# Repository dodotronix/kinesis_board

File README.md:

# KINESIS BOARD SUPPORTING QMK DRIVER
This project is just small redesign of the Tkint board (https://github.com/kinx-project/kint)

# REQUIREMENTS 
- to be able to properly open the schematics, download following libraries
    - https://github.com/dodotronix/dodo_klibs

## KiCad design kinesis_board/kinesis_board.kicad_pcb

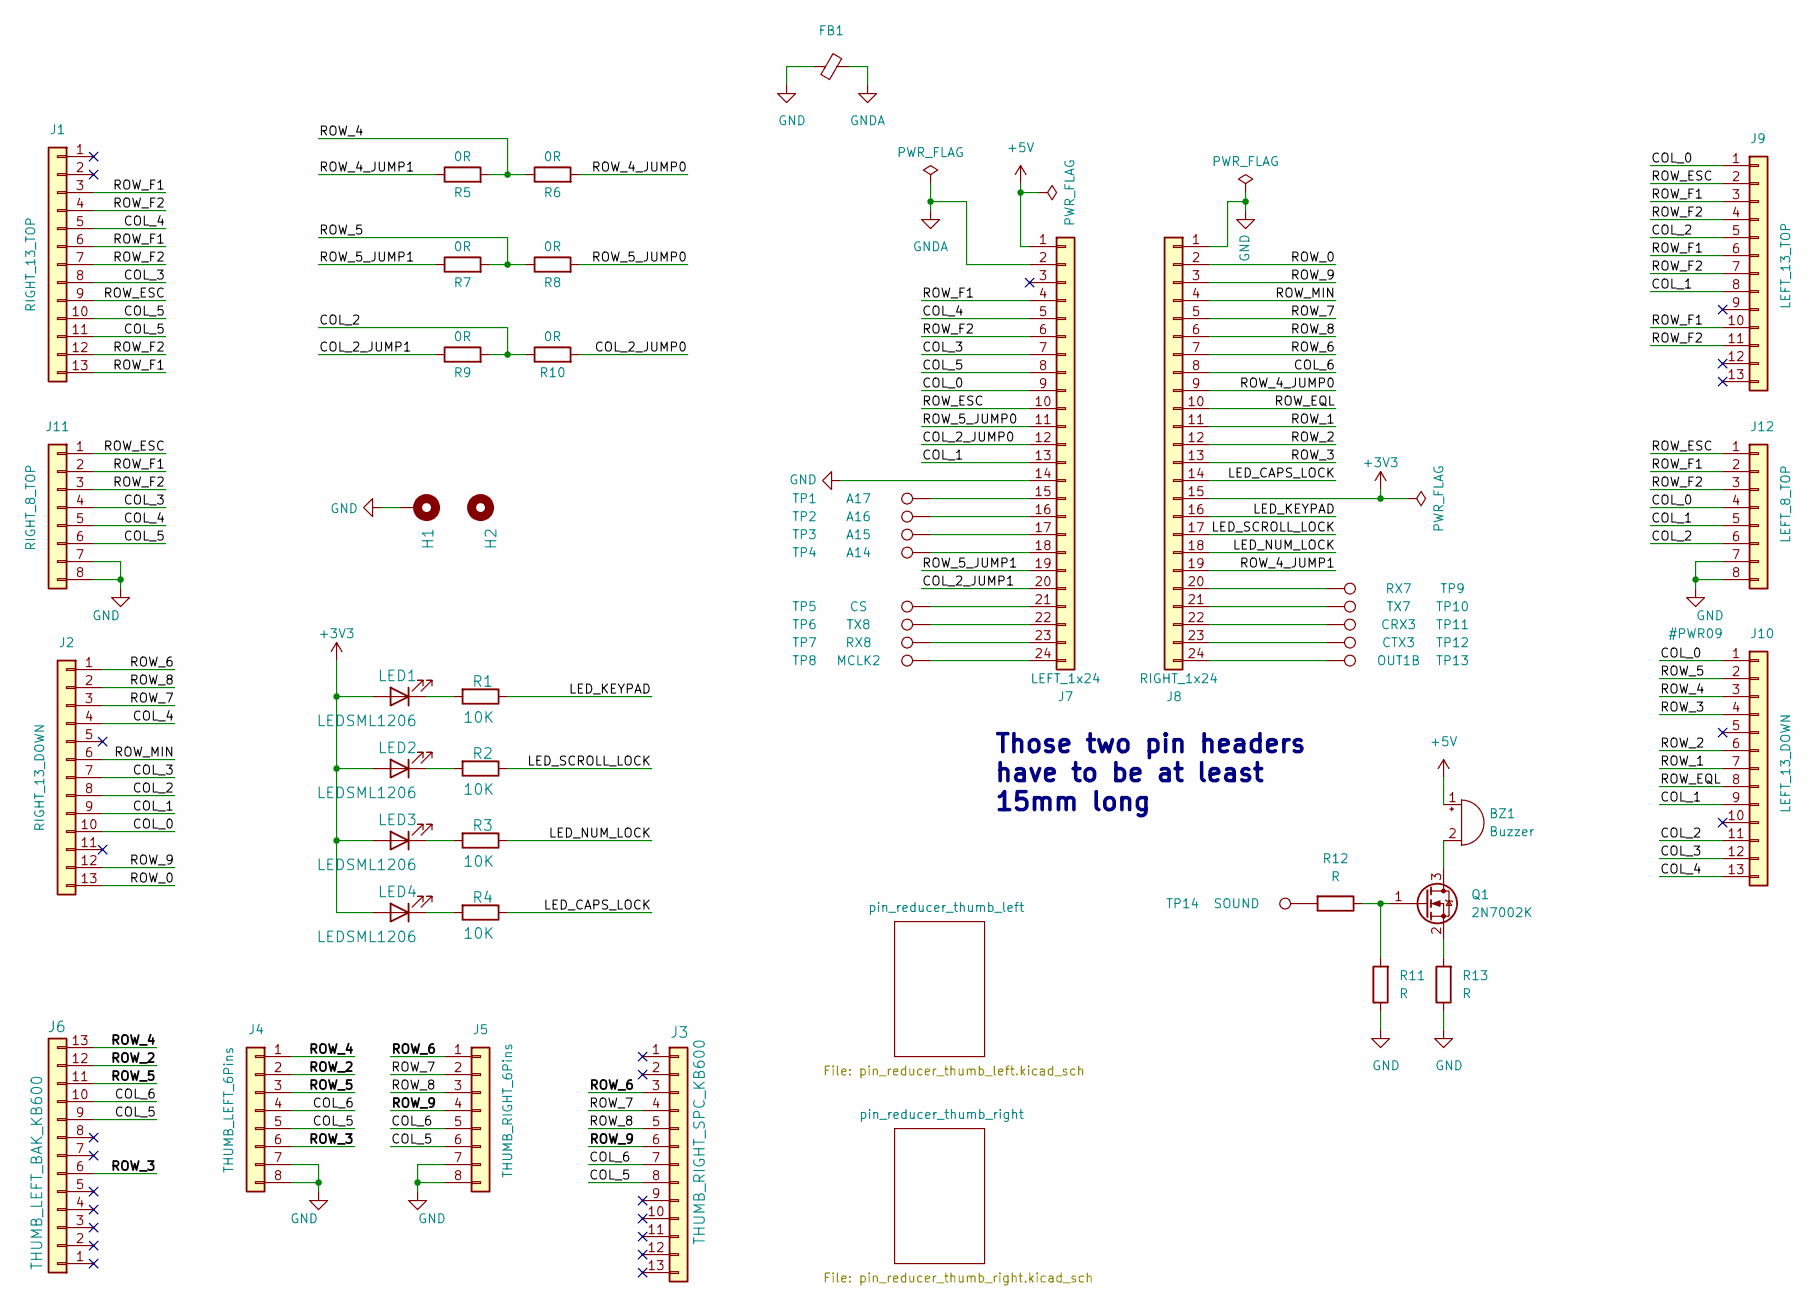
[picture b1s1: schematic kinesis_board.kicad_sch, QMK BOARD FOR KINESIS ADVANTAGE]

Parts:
BZ1: Buzzer; Buzzer_12x9.5RM7.6
FB1: FerriteBead; L_0805_2012Metric_Pad1.05x1.20mm_HandSolder
H1: mounting pad; MountingHole_4.3mm_M4_Pad
H2: mounting pad; MountingHole_6mm
J1: RIGHT_13_TOP; Molex-39-53-2135; MPN 39-53-2135; digikeypn WM14526-ND
J2: RIGHT_13_DOWN; Molex-39-53-2135; MPN 39-53-2135; digikeypn WM14526-ND
J3: THUMB_RIGHT_SPC_KB600; Molex-39-53-2135; MPN 39-53-2135; digikeypn WM14526-ND
J4: THUMB_LEFT_6Pins; 84953-6
J5: THUMB_RIGHT_6Pins; 84953-6
J6: THUMB_LEFT_BAK_KB600; Molex-39-53-2135; MPN 39-53-2135; digikeypn WM14526-ND
J7: LEFT_1x24; PinHeader_1x24_P2.54mm_Vertical
J8: RIGHT_1x24; PinHeader_1x24_P2.54mm_Vertical
J9: LEFT_13_TOP; Molex-39-53-2135; MPN 39-53-2135; digikeypn WM14526-ND
J10: LEFT_13_DOWN; Molex-39-53-2135; MPN 39-53-2135; digikeypn WM14526-ND
J11: RIGHT_8_TOP; 84953-6
J12: LEFT_8_TOP; 84953-6
LED1, LED2, LED3, LED4: LEDSML1206; LED_1206_3216Metric_Pad1.42x1.75mm_HandSolder; MPN APT3216QBC/D; digikeypn 754-1439-1-ND
Q1: 2N7002K; SOT-23
R1, R2, R3, R4: 10K; R_1206_3216Metric_Pad1.30x1.75mm_HandSolder; MPN CRCW120610K0FKEAC; digikeypn 541-3983-1-ND
R5, R6, R7, R8, R9, R10: 0R; R_1206_3216Metric_Pad1.30x1.75mm_HandSolder
R11, R12, R13: R; R_0805_2012Metric_Pad1.20x1.40mm_HandSolder
TP1: A17; TestPoint_Pad_D2.0mm
TP2: A16; TestPoint_Pad_D2.0mm
TP3: A15; TestPoint_Pad_D2.0mm
TP4: A14; TestPoint_Pad_D2.0mm
TP5: CS; TestPoint_Pad_D2.0mm
TP6: TX8; TestPoint_Pad_D2.0mm
TP7: RX8; TestPoint_Pad_D2.0mm
TP8: MCLK2; TestPoint_Pad_D2.0mm
TP9: RX7; TestPoint_Pad_D2.0mm
TP10: TX7; TestPoint_Pad_D2.0mm
TP11: CRX3; TestPoint_Pad_D2.0mm
TP12: CTX3; TestPoint_Pad_D2.0mm
TP13: OUT1B; TestPoint_Pad_D2.0mm
TP14: SOUND; TestPoint_Pad_D2.0mm

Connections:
+3V3: J8.15, LED1.2 (A), LED2.2 (A), LED3.2 (A), LED4.2 (A)
+5V: BZ1.1 (-), J7.1
/COL_0: J2.10, J7.9, J9.1, J10.1, J12.4
/COL_1: J2.9, J7.13, J9.8, J10.9, J12.5
/COL_2: J2.8, J9.5, J10.11, J12.6, R9.2, R10.1
/COL_2_JUMP0: J7.12, R10.2
/COL_2_JUMP1: J7.20, R9.1
/COL_3: J1.8, J2.7, J7.7, J10.12, J11.4
/COL_4: J1.5, J2.4, J7.5, J10.13, J11.5
/COL_5: J1.10, J1.11, J3.8, J4.5, J5.6, J6.9, J7.8, J11.6
/COL_6: J3.7, J4.4, J5.5, J6.10, J8.8
/LED_CAPS_LOCK: J8.14, R4.1
/LED_KEYPAD: J8.16, R1.1
/LED_NUM_LOCK: J8.18, R3.1
/LED_SCROLL_LOCK: J8.17, R2.1
/ROW_0: J2.13, J8.2
/ROW_1: J8.11, J10.7
/ROW_2: J4.2, J6.12, J8.12, J10.6
/ROW_3: J4.6, J6.6, J8.13, J10.4
/ROW_4: J4.1, J6.13, J10.3, R5.2, R6.1
/ROW_4_JUMP0: J8.9, R6.2
/ROW_4_JUMP1: J8.19, R5.1
/ROW_5: J4.3, J6.11, J10.2, R7.2, R8.1
/ROW_5_JUMP0: J7.11, R8.2
/ROW_5_JUMP1: J7.19, R7.1
/ROW_6: J2.1, J3.3, J5.1, J8.7
/ROW_7: J2.3, J3.4, J5.2, J8.5
/ROW_8: J2.2, J3.5, J5.3, J8.6
/ROW_9: J2.12, J3.6, J5.4, J8.3
/ROW_EQL: J8.10, J10.8
/ROW_ESC: J1.9, J7.10, J9.2, J11.1, J12.1
/ROW_F1: J1.3, J1.6, J1.13, J7.4, J9.3, J9.6, J9.10, J11.2, J12.2
/ROW_F2: J1.4, J1.7, J1.12, J7.6, J9.4, J9.7, J9.11, J11.3, J12.3
/ROW_MIN: J2.6, J8.4
GND: FB1.1, H1.1, J4.7, J4.8, J5.7, J5.8, J7.14, J8.1, J11.7, J11.8, J12.7, J12.8, R11.1, R13.1; also elsewhere on the board
GNDA: FB1.2, J7.2
unnamed: BZ1.2 (+), Q1.3 (D)
unnamed: J7.15, TP1.1
unnamed: J7.16, TP2.1
unnamed: J7.17, TP3.1
unnamed: J7.18, TP4.1
unnamed: J7.21, TP5.1
unnamed: J7.22, TP6.1
unnamed: J7.23, TP7.1
unnamed: J7.24, TP8.1
unnamed: J8.20, TP9.1
unnamed: J8.21, TP10.1
unnamed: J8.22, TP11.1
unnamed: J8.23, TP12.1
unnamed: J8.24, TP13.1
unnamed: LED1.1 (K), R1.2
unnamed: LED2.1 (K), R2.2
unnamed: LED3.1 (K), R3.2
unnamed: LED4.1 (K), R4.2
unnamed: Q1.1 (G), R11.2, R12.1
unnamed: Q1.2 (S), R13.2
unnamed: R12.2, TP14.1

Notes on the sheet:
Those two pin headers have to be at least 15mm long

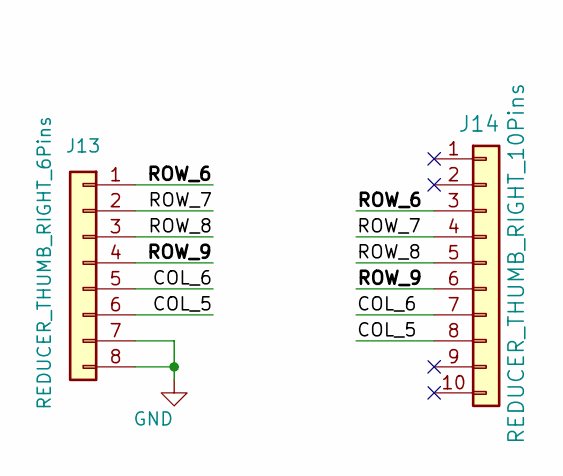
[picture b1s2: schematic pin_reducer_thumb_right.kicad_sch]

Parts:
J13: REDUCER_THUMB_RIGHT_6Pins; 84953-6
J14: REDUCER_THUMB_RIGHT_10Pins; PinHeader_1x10_P2.54mm_Vertical; MPN 39-53-2135; digikeypn WM14526-ND

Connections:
/pin_reducer_thumb_right/COL_5: J13.6, J14.8
/pin_reducer_thumb_right/COL_6: J13.5, J14.7
/pin_reducer_thumb_right/ROW_6: J13.1, J14.3
/pin_reducer_thumb_right/ROW_7: J13.2, J14.4
/pin_reducer_thumb_right/ROW_8: J13.3, J14.5
/pin_reducer_thumb_right/ROW_9: J13.4, J14.6
GND: J13.7, J13.8; also elsewhere on the board

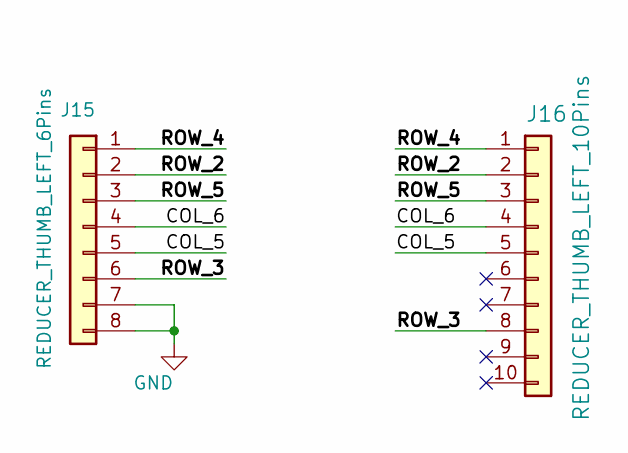
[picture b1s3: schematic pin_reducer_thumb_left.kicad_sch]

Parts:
J15: REDUCER_THUMB_LEFT_6Pins; 84953-6
J16: REDUCER_THUMB_LEFT_10Pins; PinHeader_1x10_P2.54mm_Vertical; MPN 39-53-2135; digikeypn WM14526-ND

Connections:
/pin_reducer_thumb_left/COL_5: J15.5, J16.5
/pin_reducer_thumb_left/COL_6: J15.4, J16.4
/pin_reducer_thumb_left/ROW_2: J15.2, J16.2
/pin_reducer_thumb_left/ROW_3: J15.6, J16.8
/pin_reducer_thumb_left/ROW_4: J15.1, J16.1
/pin_reducer_thumb_left/ROW_5: J15.3, J16.3
GND: J15.7, J15.8; also elsewhere on the board

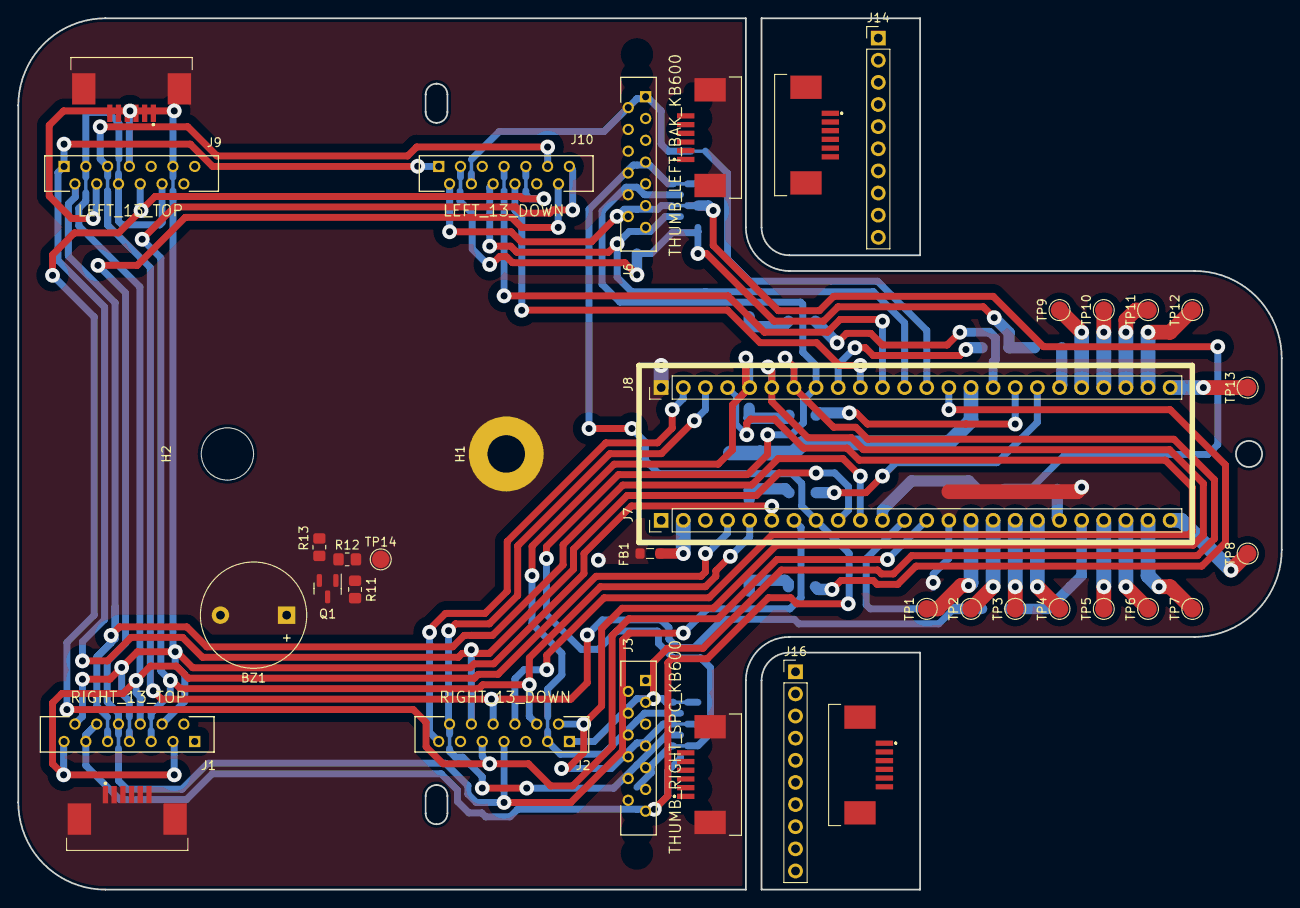
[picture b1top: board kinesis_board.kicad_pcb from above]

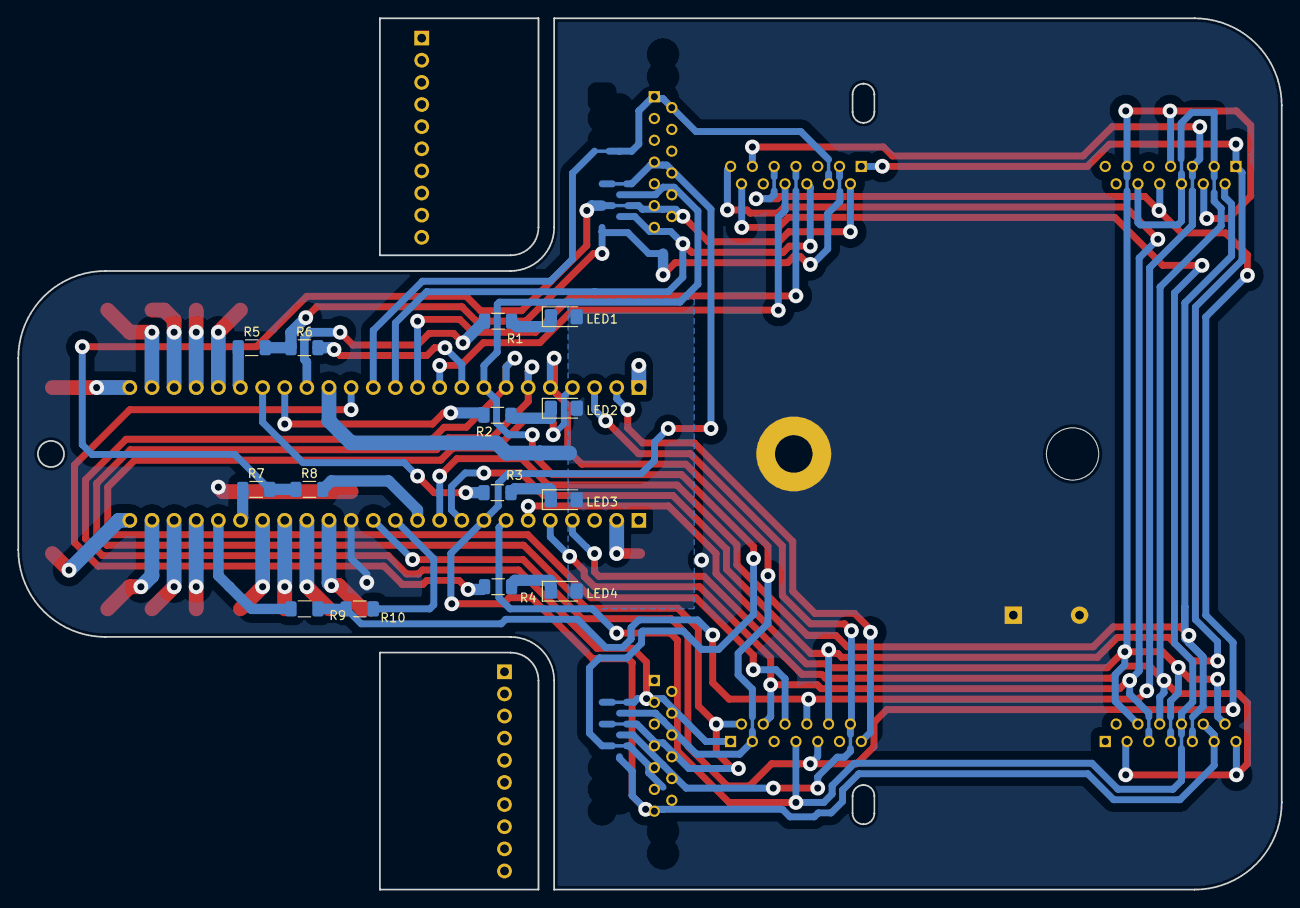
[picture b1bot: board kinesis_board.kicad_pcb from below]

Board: 2 copper layers, 145.0 x 100.0 mm, 52 parts (14 on the bottom side), 69 nets.

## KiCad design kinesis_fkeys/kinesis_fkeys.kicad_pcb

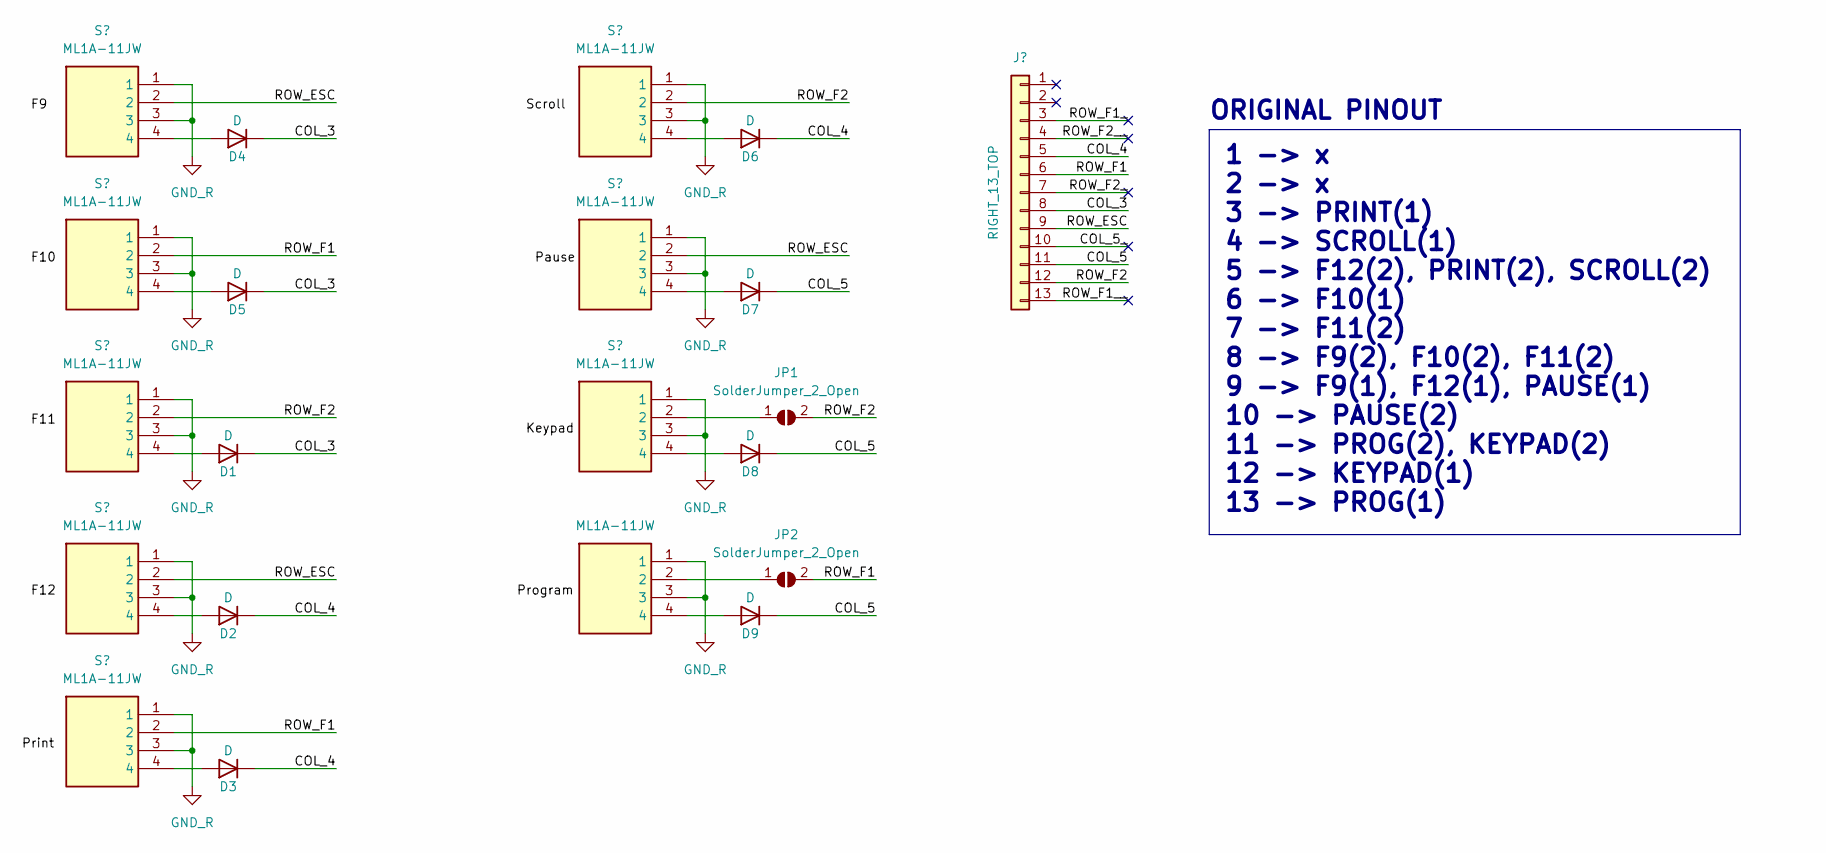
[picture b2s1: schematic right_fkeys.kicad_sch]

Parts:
D1, D2, D3, D4, D5, D6, D7, D8, D9: D; D_MiniMELF_Handsoldering
J1: RIGHT_13_TOP; Molex-39-53-2134; MPN 39-53-2135; digikeypn WM14526-ND
JP1, JP2: SolderJumper_2_Open; SolderJumper-2_P1.3mm_Open_Pad1.0x1.5mm
S1, S2, S3, S4, S5, S6, S7, S8, S9: ML1A-11JW; ML1A11JW; Mouser Part Number 540-ML1A-11JW

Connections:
/right_fkeys/COL_3: D1.1 (K), D4.1 (K), D5.1 (K), J1.8
/right_fkeys/COL_4: D2.1 (K), D3.1 (K), D6.1 (K), J1.5
/right_fkeys/COL_5: D7.1 (K), D8.1 (K), D9.1 (K), J1.11
/right_fkeys/COL_5_: J1.10
/right_fkeys/ROW_ESC: J1.9, S1.2, S4.2, S7.2
/right_fkeys/ROW_F1: J1.6, JP2.2 (B), S2.2, S5.2
/right_fkeys/ROW_F1_: J1.3
/right_fkeys/ROW_F1__: J1.13
/right_fkeys/ROW_F2: J1.12, JP1.2 (B), S3.2, S6.2
/right_fkeys/ROW_F2_: J1.7
/right_fkeys/ROW_F2__: J1.4
GND_R: S1.1, S1.3, S2.1, S2.3, S3.1, S3.3, S4.1, S4.3, S5.1, S5.3, S6.1, S6.3, S7.1, S7.3, S8.1, S8.3, S9.1, S9.3
unnamed: D1.2 (A), S3.4
unnamed: D2.2 (A), S4.4
unnamed: D3.2 (A), S5.4
unnamed: D4.2 (A), S1.4
unnamed: D5.2 (A), S2.4
unnamed: D6.2 (A), S6.4
unnamed: D7.2 (A), S7.4
unnamed: D8.2 (A), S8.4
unnamed: D9.2 (A), S9.4
unnamed: JP1.1 (A), S8.2
unnamed: JP2.1 (A), S9.2

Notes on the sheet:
1 -> x 2 -> x 3 -> PRINT(1) 4 -> SCROLL(1) 5 -> F12(2), PRINT(2), SCROLL(2) 6 -> F10(1) 7 -> F11(2) 8 -> F9(2), F10(2), F11(2) 9 -> F9(1), F12(1), PAUSE(1) 10 -> PAUSE(2) 11 -> PROG(2), KEYPAD(2) 12 -> KEYPAD(1) 13 -> PROG(1)
ORIGINAL PINOUT

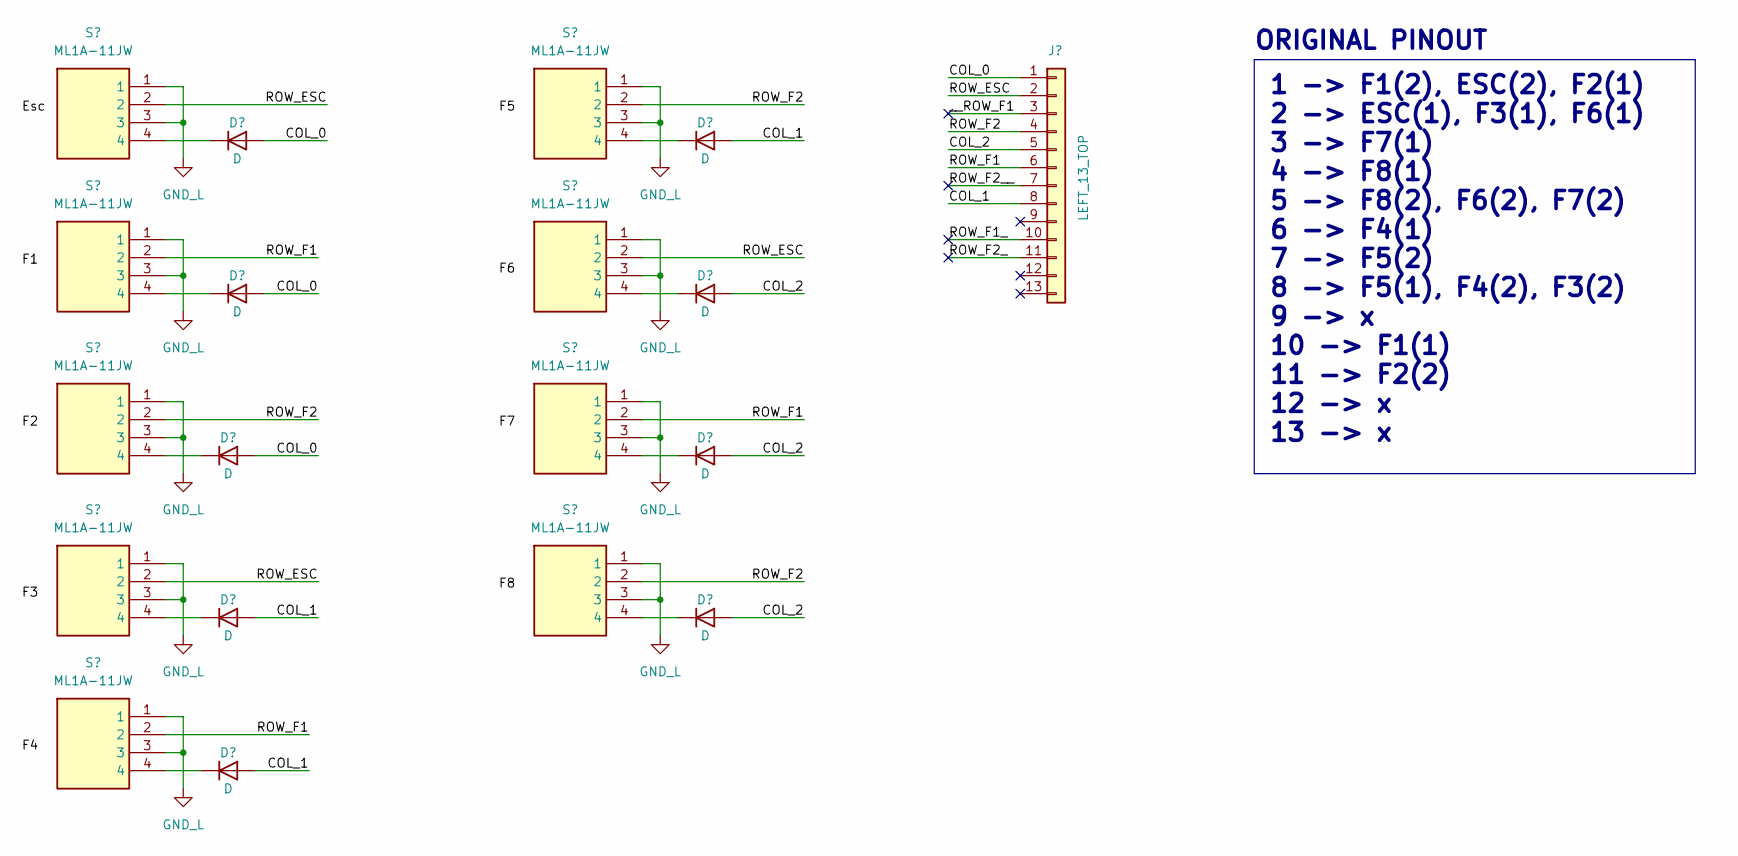
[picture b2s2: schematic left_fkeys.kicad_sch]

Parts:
D10, D11, D12, D13, D14, D15, D16, D17, D18: D; D_MiniMELF_Handsoldering
J2: LEFT_13_TOP; Molex-39-53-2134; MPN 39-53-2135; digikeypn WM14526-ND
S10, S11, S12, S13, S14, S15, S16, S17, S18: ML1A-11JW; ML1A11JW; Mouser Part Number 540-ML1A-11JW

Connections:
/left_fkeys/COL_0: D10.2 (A), D13.2 (A), D14.2 (A), J2.1
/left_fkeys/COL_1: D11.2 (A), D12.2 (A), D15.2 (A), J2.8
/left_fkeys/COL_2: D16.2 (A), D17.2 (A), D18.2 (A), J2.5
/left_fkeys/ROW_ESC: J2.2, S10.2, S13.2, S16.2
/left_fkeys/ROW_F1: J2.6, S11.2, S14.2, S17.2
/left_fkeys/ROW_F1_: J2.10
/left_fkeys/ROW_F2: J2.4, S12.2, S15.2, S18.2
/left_fkeys/ROW_F2_: J2.11
/left_fkeys/ROW_F2__: J2.7
/left_fkeys/__ROW_F1: J2.3
GND_L: S10.1, S10.3, S11.1, S11.3, S12.1, S12.3, S13.1, S13.3, S14.1, S14.3, S15.1, S15.3, S16.1, S16.3, S17.1, S17.3, S18.1, S18.3
unnamed: D10.1 (K), S12.4
unnamed: D11.1 (K), S13.4
unnamed: D12.1 (K), S14.4
unnamed: D13.1 (K), S10.4
unnamed: D14.1 (K), S11.4
unnamed: D15.1 (K), S15.4
unnamed: D16.1 (K), S16.4
unnamed: D17.1 (K), S17.4
unnamed: D18.1 (K), S18.4

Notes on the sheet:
1 -> F1(2), ESC(2), F2(1) 2 -> ESC(1), F3(1), F6(1) 3 -> F7(1) 4 -> F8(1) 5 -> F8(2), F6(2), F7(2) 6 -> F4(1) 7 -> F5(2) 8 -> F5(1), F4(2), F3(2) 9 -> x 10 -> F1(1) 11 -> F2(2) 12 -> x 13 -> x
ORIGINAL PINOUT

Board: 2 copper layers, 40 parts (20 on the bottom side), 34 nets, no tracks yet.

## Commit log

2022-10-02 new empty readme
2022-11-06 created kicad project and schematics with components
2022-11-06 finished drawing of the schematics -- needs to be checked before pcb drawing
2022-12-27 added info about required libraries
2022-12-27 first revision of board - routing needs to be optimized
2022-12-29 adjusted placement of the pin headers and connectors - routing not finished
2023-01-03 finished routing of revision 2.0
2023-01-03 generated gerber files for home fabrication
2023-01-06 adjusted size of the board
2023-01-06 generated files for fabrication
2023-01-11 added forgotten vias
2023-10-10 created schematics connections for the two fkey keyboards
2023-10-11 created basic shape for the pcb
2023-10-12 modified pcb cut edge
2023-10-14 buttons schematics verified and placed on the pcb on exact spots
2023-10-15 added diods againts ghosting on the both PCBs
2023-10-15 added TE 84953 6 pin connectors to reduce amount of tracks
2023-10-15 fixed wrong amount pins on the footprint and sorted pinout on the connectors
2023-10-15 added fpc connector to be able to connect new fkeys keypads - not routed yet
2023-10-28 updated pcb to use smalle connector and removed the pin headers from the main pcb
2023-10-28 positioning of components and added filled zones
2023-10-28 possitioned componentst on the pcb left
2023-11-28 created layout - needs to be modified a bit
2023-12-03 finished second version of the layout
2023-12-05 finished layout with successful drc
2023-12-05 added dimensions of pcb
2023-12-10 updated silkcreen text
2025-02-20 removed properties in schematics and updated kicad project version
